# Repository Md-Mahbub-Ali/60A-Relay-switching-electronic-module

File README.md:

# 60A-Relay-switching-electronic-module
# Designed with Autodesk Eagle
 Market available two 30A relay will operate at a time  
 10A normal rocker switch will drive the 60A Relay switch

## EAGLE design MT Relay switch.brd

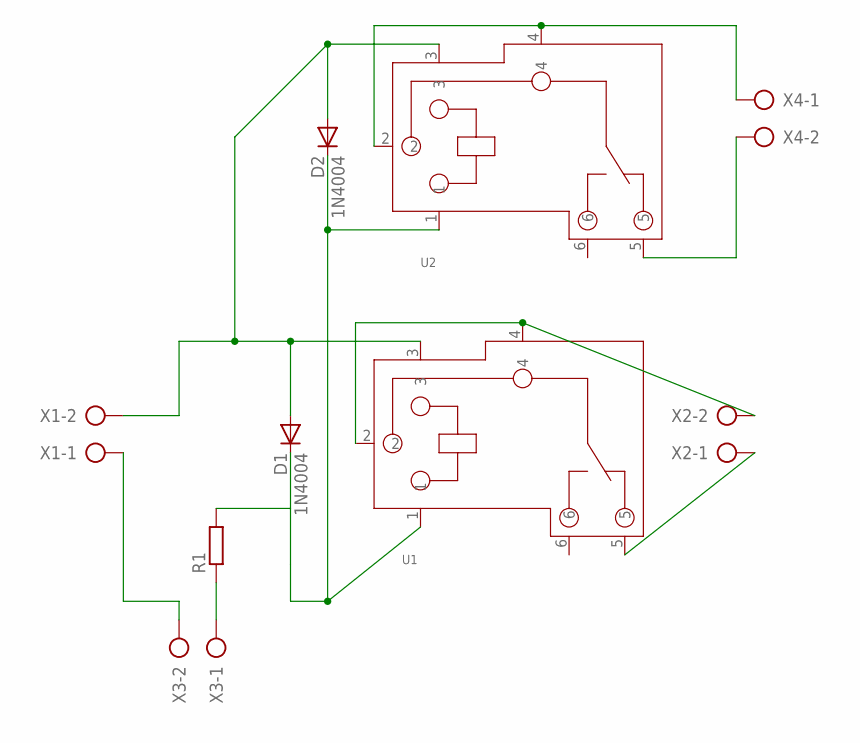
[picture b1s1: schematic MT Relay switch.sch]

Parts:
D1, D2: 1N4004; DO41-10
R1: R-EU_0204/7; 0204/7
U1, U2: RELAY-SLA-05VDC-SL-C; 6P-19.8H
X1, X2, X3, X4: AK300/2

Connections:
unnamed: U1.5, X2.1
unnamed: D1.A, D2.A, U1.3, U2.3, X1.2
unnamed: U1.2, U1.4, X2.2
unnamed: X1.1, X3.2
unnamed: R1.1, X3.1
unnamed: D1.C, D2.C, R1.2, U1.1, U2.1
unnamed: U2.2, U2.4, X4.1
unnamed: U2.5, X4.2

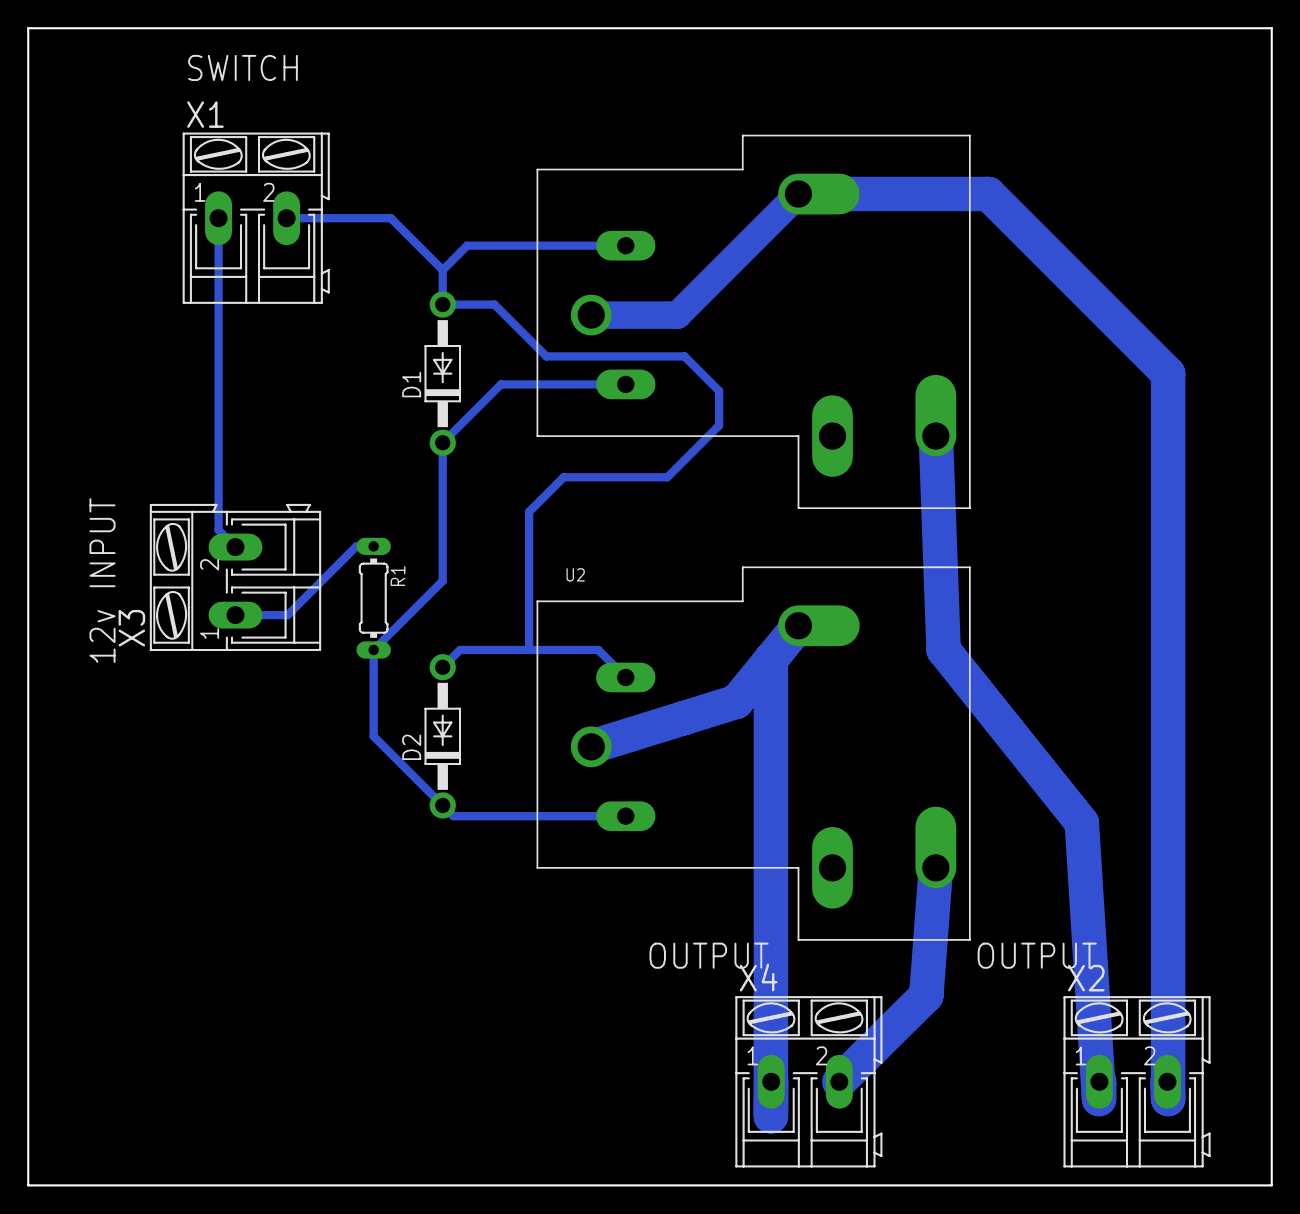
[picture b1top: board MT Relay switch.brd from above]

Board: 2 copper layers, 91.4 x 85.1 mm, 9 parts (0 on the bottom side), 8 nets.
